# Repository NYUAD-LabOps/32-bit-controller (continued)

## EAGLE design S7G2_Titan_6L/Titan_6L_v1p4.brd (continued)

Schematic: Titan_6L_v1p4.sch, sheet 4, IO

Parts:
J8, J9, J11, J23, J25, J26, J27, J28, J29, J30, J31, J32, J33, J34: CONN_530470210_PICOBLADE_X_2; CON_530470210_MOL
J10, J13, J14, J15, J16, J17, J18, J19, J20, J21, J22, J24: CONN_530470410_PICOBLADE_X_4; CON_530470410_MOL
J12: 10-pos; 2X5
LED3, LED4, LED5, LED6, LED7, LED8, LED9, LED10, LED11, LED12, LED13, LED14, LED15, LED16: Green; 0805
R1, R2, R96, R97, R102, R103, R105, R106: 100K; 0402
R3, R12, R91, R93: 500R0; 0402
R4, R8, R61, R67, R70, R73, R78, R81, R84, R88: 2.2K; 0402
R6, R9, R11, R27, R62, R68, R71, R76, R79, R82, R85, R89, R92, R95: 470R0; 0402
R7, R10, R63, R69, R72, R77, R80, R83, R86, R90: 10K0; 0402
R28, R29, R30, R31, R32, R33, R34, R35, R36, R37, R38, R39, R40, R41, R42, R43, R44, R45, R46, R47, R48, R49, R50, R51, R52, R53, R54, R55, R56, R57, R58, R59, R60, R64, R65, R66: 33R0; 0402
TH01, TH02, TH03, TH04, TH05, TH06, TH07, TH08: CONN_530470210_PICOBLADE_X_2; CON_530470210_MOL
U7, U8, U9, U10, U11, U12, U13, U14, U15, U16, U17, U18, U19, U20, U21, U22, U23, U24, U25, U26, U27, U28, U29, U30, U31, U32, U33, U34, U35, U36, U37, U38, U39, U40, U41, U42, U43, U44, U45, U46, U47, U48, U49, U50, U51, U52, U53, U54, U55, U56: BC846BW; SOT323

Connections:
ESTOP: R89.2, R90.2, U53.2 (E(1)); also elsewhere on the board
GND: J8.1, J9.1, J10.1, J13.1, J14.1, J15.1, J16.1, J17.1, J18.1, J19.1, J20.1, J21.1, J22.1, J23.1, J24.1, J25.1, J26.1, J27.1, J28.1, J29.1, J30.1, J31.1, LED3.2 (C), LED4.2 (C), LED6.2 (C), LED7.2 (C), LED8.2 (C), LED9.2 (C), LED10.2 (C), LED11.2 (C), LED12.2 (C), LED13.2 (C), R7.1, R10.1, R63.1, R69.1, R72.1, R77.1, R80.1, R83.1, R86.1, R90.1, TH01.1, TH02.1, TH03.1, TH04.1, TH05.1, TH06.1, TH07.1, TH08.1, U9.2 (E(1)), U10.2 (E(1)), U11.2 (E(1)), U12.2 (E(1)), U13.2 (E(1)), U14.2 (E(1)), U15.2 (E(1)), U16.2 (E(1)), U17.2 (E(1)), U18.2 (E(1)), U19.2 (E(1)), U20.2 (E(1)), U21.2 (E(1)), U22.2 (E(1)), U23.2 (E(1)), U24.2 (E(1)), U25.2 (E(1)), U26.2 (E(1)), U27.2 (E(1)), U28.2 (E(1)), U29.2 (E(1)), U30.2 (E(1)), U31.2 (E(1)), U32.2 (E(1)), U33.2 (E(1)), U34.2 (E(1)), U35.2 (E(1)), U36.2 (E(1)), U37.2 (E(1)), U38.2 (E(1)), U39.2 (E(1)), U40.2 (E(1)), U41.2 (E(1)), U42.2 (E(1)), U45.2 (E(1)), U46.2 (E(1)), U47.2 (E(1)), U54.2 (E(1)), U55.2 (E(1)), U56.2 (E(1)); also elsewhere on the board
LS_01: R6.2, R7.2, U7.2 (E(1)); also elsewhere on the board
LS_02: R9.2, R10.2, U8.2 (E(1)); also elsewhere on the board
LS_03: R62.2, R63.2, U43.2 (E(1)); also elsewhere on the board
LS_04: R68.2, R69.2, U44.2 (E(1)); also elsewhere on the board
LS_05: R71.2, R72.2, U48.2 (E(1)); also elsewhere on the board
LS_06: R76.2, R77.2, U49.2 (E(1)); also elsewhere on the board
LS_07: R79.2, R80.2, U50.2 (E(1)); also elsewhere on the board
LS_08: R82.2, R83.2, U51.2 (E(1)); also elsewhere on the board
LS_09: R85.2, R86.2, U52.2 (E(1)); also elsewhere on the board
LS_RET: J8.2, J9.2, J23.2, J25.2, J26.2, J27.2, J28.2, J29.2, J30.2, J31.2, R4.1, R8.1, R61.1, R67.1, R70.1, R73.1, R78.1, R81.1, R84.1, R88.1
M1_DIR: R29.1; also elsewhere on the board
M1_ENABLE: R30.1; also elsewhere on the board
M1_STEP: R28.1; also elsewhere on the board
M2_DIR: R32.1; also elsewhere on the board
M2_ENABLE: R33.1; also elsewhere on the board
M2_STEP: R31.1; also elsewhere on the board
M3_DIR: R35.1; also elsewhere on the board
M3_ENABLE: R36.1; also elsewhere on the board
M3_STEP: R34.1; also elsewhere on the board
M4_DIR: R38.1; also elsewhere on the board
M4_ENABLE: R39.1; also elsewhere on the board
M4_STEP: R37.1; also elsewhere on the board
M5_DIR: R41.1; also elsewhere on the board
M5_ENABLE: R42.1; also elsewhere on the board
M5_STEP: R40.1; also elsewhere on the board
M6_DIR: R47.1; also elsewhere on the board
M6_ENABLE: R48.1; also elsewhere on the board
M6_STEP: R46.1; also elsewhere on the board
M7_DIR: R53.1; also elsewhere on the board
M7_ENABLE: R54.1; also elsewhere on the board
M7_STEP: R52.1; also elsewhere on the board
M8_DIR: R59.1; also elsewhere on the board
M8_ENABLE: R60.1; also elsewhere on the board
M8_STEP: R58.1; also elsewhere on the board
M9_DIR: R44.1; also elsewhere on the board
M9_ENABLE: R45.1; also elsewhere on the board
M9_STEP: R43.1; also elsewhere on the board
M10_DIR: R56.1; also elsewhere on the board
M10_ENABLE: R57.1; also elsewhere on the board
M10_STEP: R55.1; also elsewhere on the board
M11_DIR: R65.1; also elsewhere on the board
M11_ENABLE: R66.1; also elsewhere on the board
M11_STEP: R64.1; also elsewhere on the board
M12_DIR: R50.1; also elsewhere on the board
M12_ENABLE: R51.1; also elsewhere on the board
M12_STEP: R49.1; also elsewhere on the board
MO_DIR: J10.3, J13.3, J14.3, J15.3, J16.3, J17.3, J18.3, J19.3, J20.3, J21.3, J22.3, J24.3, U10.3 (C(3)), U13.3 (C(3)), U16.3 (C(3)), U19.3 (C(3)), U22.3 (C(3)), U25.3 (C(3)), U28.3 (C(3)), U31.3 (C(3)), U34.3 (C(3)), U37.3 (C(3)), U40.3 (C(3)), U46.3 (C(3))
MO_ENABLE: J10.2, J13.2, J14.2, J15.2, J16.2, J17.2, J18.2, J19.2, J20.2, J21.2, J22.2, J24.2, U11.3 (C(3)), U14.3 (C(3)), U17.3 (C(3)), U20.3 (C(3)), U23.3 (C(3)), U26.3 (C(3)), U29.3 (C(3)), U32.3 (C(3)), U35.3 (C(3)), U38.3 (C(3)), U41.3 (C(3)), U47.3 (C(3))
MO_STEP: J10.4, J13.4, J14.4, J15.4, J16.4, J17.4, J18.4, J19.4, J20.4, J21.4, J22.4, J24.4, U9.3 (C(3)), U12.3 (C(3)), U15.3 (C(3)), U18.3 (C(3)), U21.3 (C(3)), U24.3 (C(3)), U27.3 (C(3)), U30.3 (C(3)), U33.3 (C(3)), U36.3 (C(3)), U39.3 (C(3)), U45.3 (C(3))
unnamed: R4.2, U7.1 (B(2))
unnamed: LED3.1 (A), R6.1
unnamed: R29.2, U10.1 (B(2))
unnamed: R30.2, U11.1 (B(2))
unnamed: R28.2, U9.1 (B(2))
unnamed: R32.2, U13.1 (B(2))
unnamed: R33.2, U14.1 (B(2))
unnamed: R31.2, U12.1 (B(2))
unnamed: R35.2, U16.1 (B(2))
unnamed: R36.2, U17.1 (B(2))
unnamed: R34.2, U15.1 (B(2))
unnamed: R38.2, U19.1 (B(2))
unnamed: R39.2, U20.1 (B(2))
unnamed: R37.2, U18.1 (B(2))
unnamed: R41.2, U22.1 (B(2))
unnamed: R42.2, U23.1 (B(2))
unnamed: R40.2, U21.1 (B(2))
unnamed: R44.2, U25.1 (B(2))
unnamed: R45.2, U26.1 (B(2))
unnamed: R43.2, U24.1 (B(2))
unnamed: R47.2, U28.1 (B(2))
unnamed: R48.2, U29.1 (B(2))
unnamed: R46.2, U27.1 (B(2))
unnamed: R50.2, U31.1 (B(2))
unnamed: R51.2, U32.1 (B(2))
unnamed: R49.2, U30.1 (B(2))
unnamed: R53.2, U34.1 (B(2))
unnamed: R54.2, U35.1 (B(2))
unnamed: R52.2, U33.1 (B(2))
unnamed: R56.2, U37.1 (B(2))
unnamed: R57.2, U38.1 (B(2))
unnamed: R55.2, U36.1 (B(2))
unnamed: R59.2, U40.1 (B(2))
unnamed: R60.2, U41.1 (B(2))
unnamed: R58.2, U39.1 (B(2))
unnamed: R8.2, U8.1 (B(2))
unnamed: LED4.1 (A), R9.1
unnamed: R65.2, U46.1 (B(2))
unnamed: R66.2, U47.1 (B(2))
unnamed: R64.2, U45.1 (B(2))
unnamed: R3.2, U42.1 (B(2))
unnamed: R61.2, U43.1 (B(2))
unnamed: LED6.1 (A), R62.1
unnamed: R67.2, U44.1 (B(2))
unnamed: LED7.1 (A), R68.1
unnamed: R70.2, U48.1 (B(2))
unnamed: LED8.1 (A), R71.1
unnamed: R73.2, U49.1 (B(2))
unnamed: LED9.1 (A), R76.1
unnamed: R78.2, U50.1 (B(2))
unnamed: LED10.1 (A), R79.1
unnamed: R81.2, U51.1 (B(2))
unnamed: LED11.1 (A), R82.1
unnamed: R84.2, U52.1 (B(2))
unnamed: LED12.1 (A), R85.1
unnamed: R88.2, U53.1 (B(2))
unnamed: LED13.1 (A), R89.1
unnamed: J11.2, LED5.2 (C), U42.3 (C(3))
unnamed: LED5.1 (A), R11.1
unnamed: R12.2, U54.1 (B(2))
unnamed: J32.2, LED14.2 (C), U54.3 (C(3))
unnamed: LED14.1 (A), R27.1
unnamed: R91.2, U55.1 (B(2))
unnamed: J33.2, LED15.2 (C), U55.3 (C(3))
unnamed: LED15.1 (A), R92.1
unnamed: R93.2, U56.1 (B(2))
unnamed: J34.2, LED16.2 (C), U56.3 (C(3))
unnamed: LED16.1 (A), R95.1
P0_02_TH_01: R1.1, TH01.2; also elsewhere on the board
P0_04_TH_02: R2.1, TH02.2; also elsewhere on the board
P0_05_TH_03: R102.1, TH03.2; also elsewhere on the board
P0_06_TH_04: R103.1, TH04.2; also elsewhere on the board
P0_08_TH_05: R105.1, TH05.2; also elsewhere on the board
P0_09_TH_06: R106.1, TH06.2; also elsewhere on the board
P0_14_TH_07: R96.1, TH07.2; also elsewhere on the board
P0_15_TH_08: R97.1, TH08.2; also elsewhere on the board
P3_10: J12.1; also elsewhere on the board
P3_11: J12.2; also elsewhere on the board
P3_12: J12.3; also elsewhere on the board
P3_15: J12.10; also elsewhere on the board
P9_00: J12.9; also elsewhere on the board
P9_01: J12.8; also elsewhere on the board
P9_05: J12.4; also elsewhere on the board
P9_06: J12.5; also elsewhere on the board
P9_07: J12.6; also elsewhere on the board
P9_08: J12.7; also elsewhere on the board
RELAY_01: R93.1; also elsewhere on the board
RELAY_02: R91.1; also elsewhere on the board
RELAY_03: R12.1; also elsewhere on the board
RELAY_04: R3.1; also elsewhere on the board
VDD: R1.2, R2.2, R96.2, R97.2, R102.2, R103.2, R105.2, R106.2, U7.3 (C(3)), U8.3 (C(3)), U43.3 (C(3)), U44.3 (C(3)), U48.3 (C(3)), U49.3 (C(3)), U50.3 (C(3)), U51.3 (C(3)), U52.3 (C(3)), U53.3 (C(3)); also elsewhere on the board
VDD5: J11.1, J32.1, J33.1, J34.1, R11.2, R27.2, R92.2, R95.2; also elsewhere on the board

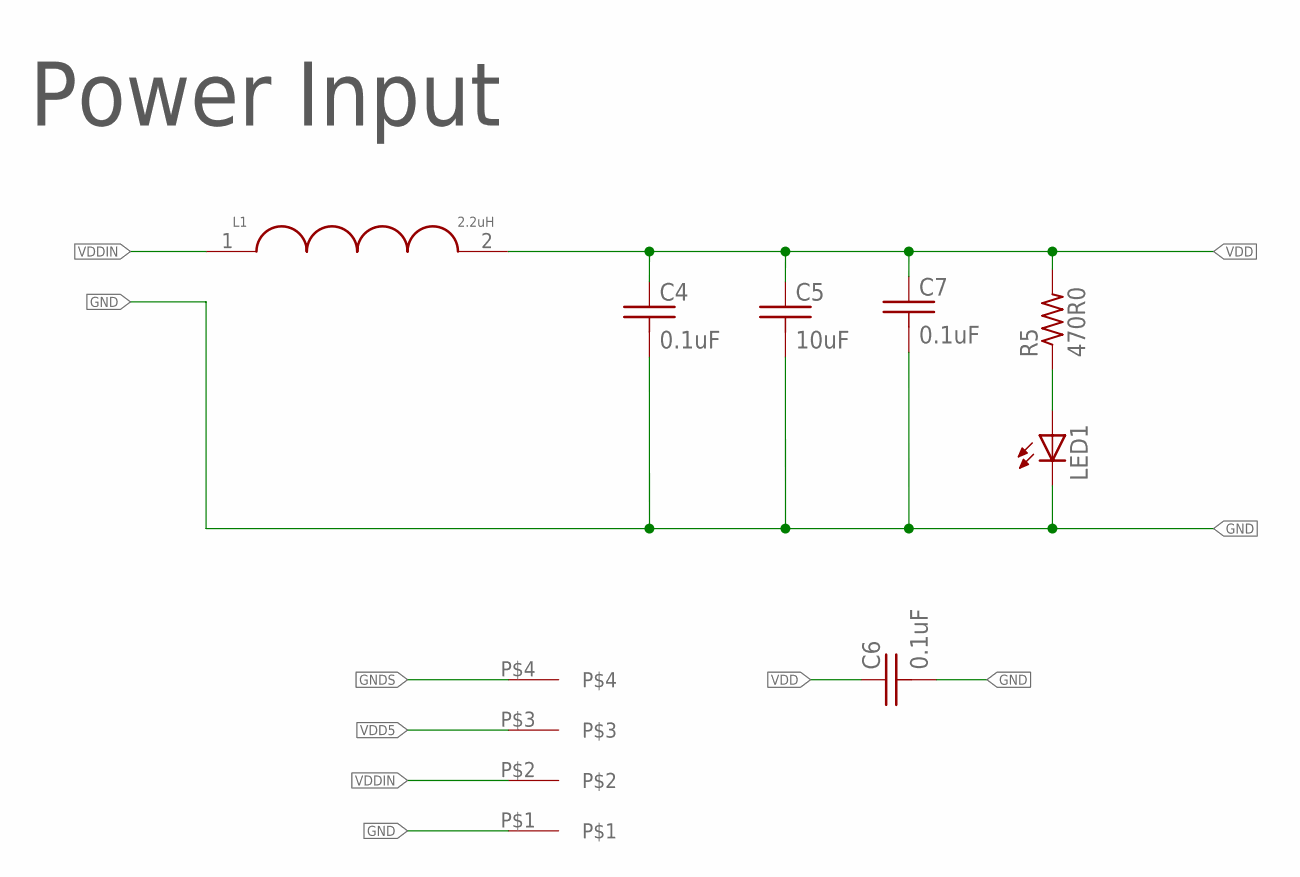
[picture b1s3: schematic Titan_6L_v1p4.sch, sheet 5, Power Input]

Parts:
C4, C6, C7: 0.1uF; 0402
C5: 10uF; 0402
J2: 4-pos; 1X4_3.81MM_PITCH
L1: 2.2uH; 1008
LED1: Green; 0805
R5: 470R0; 0402

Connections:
GND: C4.2, C5.2, C6.2, C7.2, J2.P$1, LED1.2 (C); also elsewhere on the board
GNDS: J2.P$4; also elsewhere on the board
unnamed: LED1.1 (A), R5.1
VDD: C4.1, C5.1, C6.1, C7.1, L1.2, R5.2; also elsewhere on the board
VDD5: J2.P$3; also elsewhere on the board
VDDIN: J2.P$2, L1.1

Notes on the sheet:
Power Input

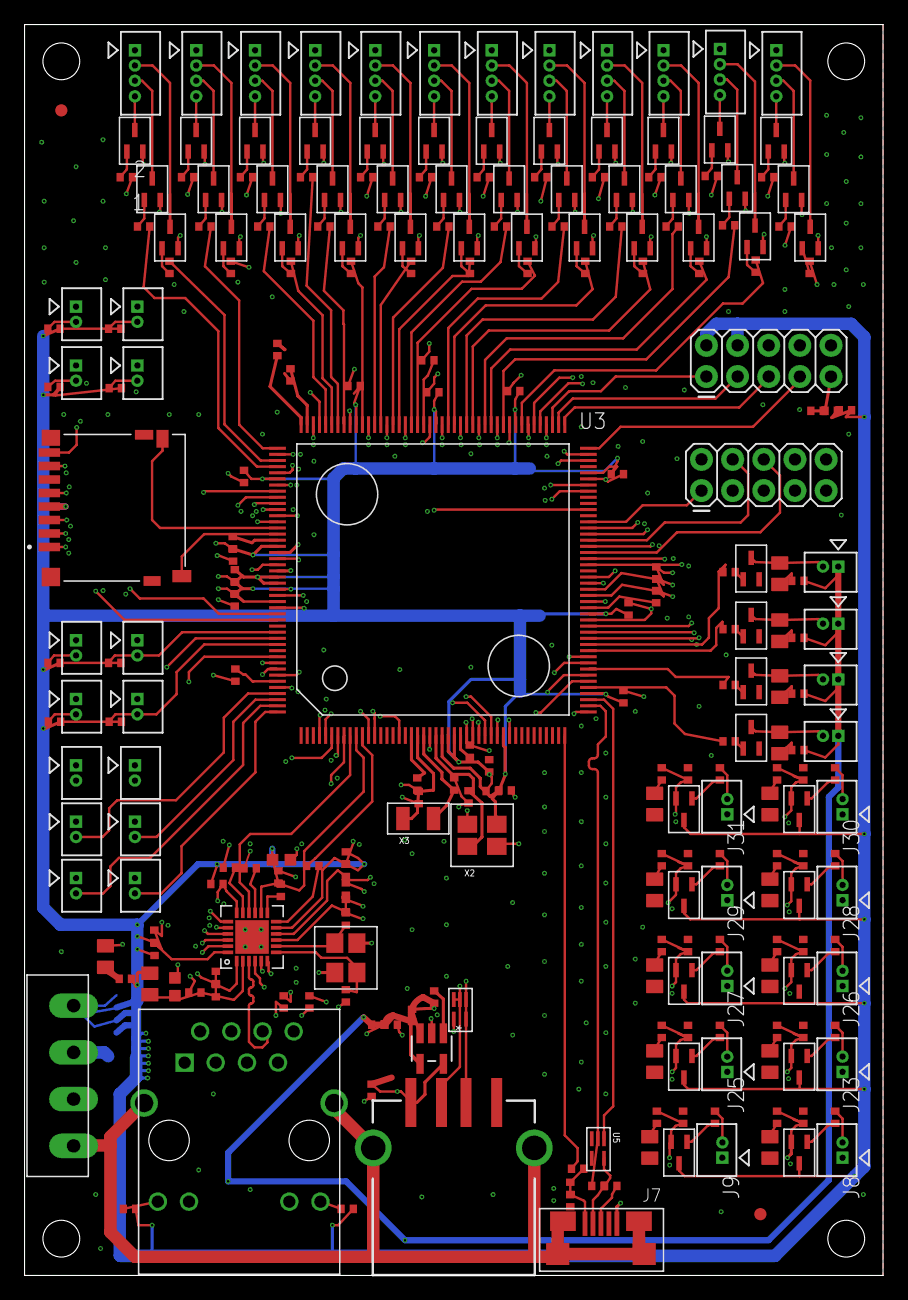
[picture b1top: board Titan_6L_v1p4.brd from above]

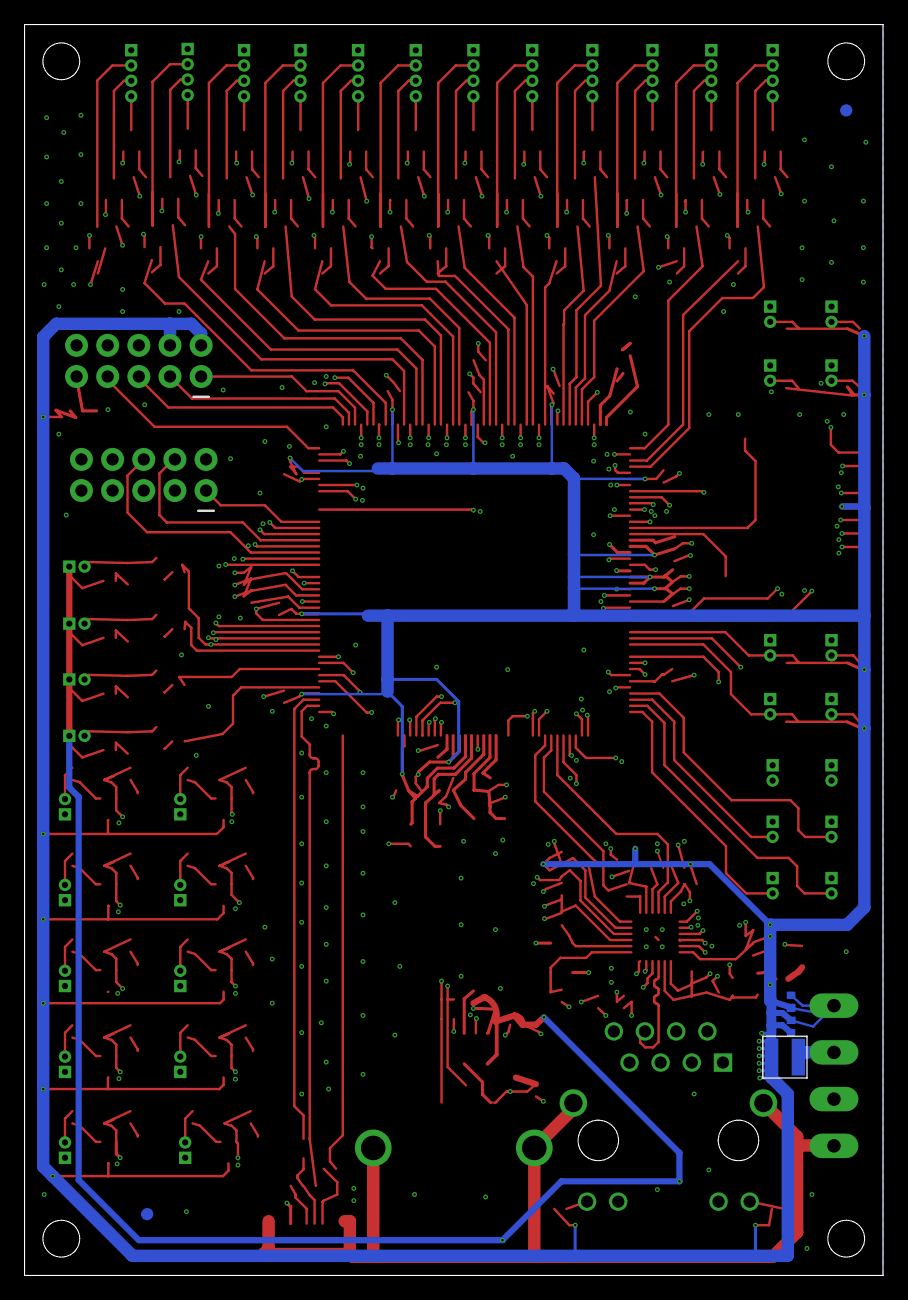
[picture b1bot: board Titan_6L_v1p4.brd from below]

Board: 6 copper layers, 70.0 x 102.0 mm, 275 parts (6 on the bottom side), 219 nets.

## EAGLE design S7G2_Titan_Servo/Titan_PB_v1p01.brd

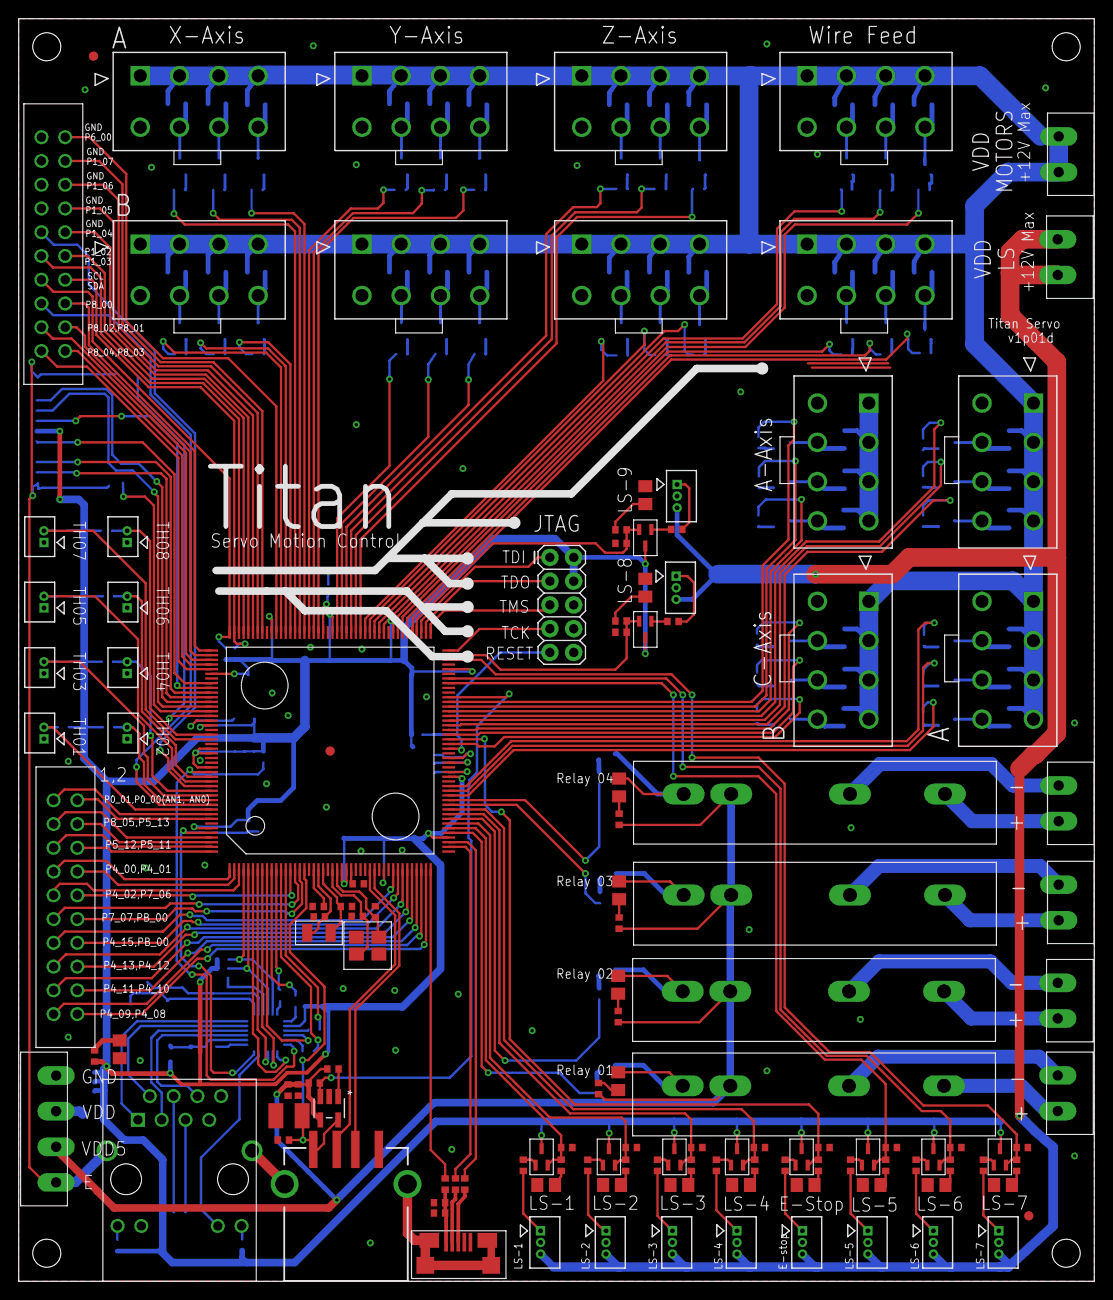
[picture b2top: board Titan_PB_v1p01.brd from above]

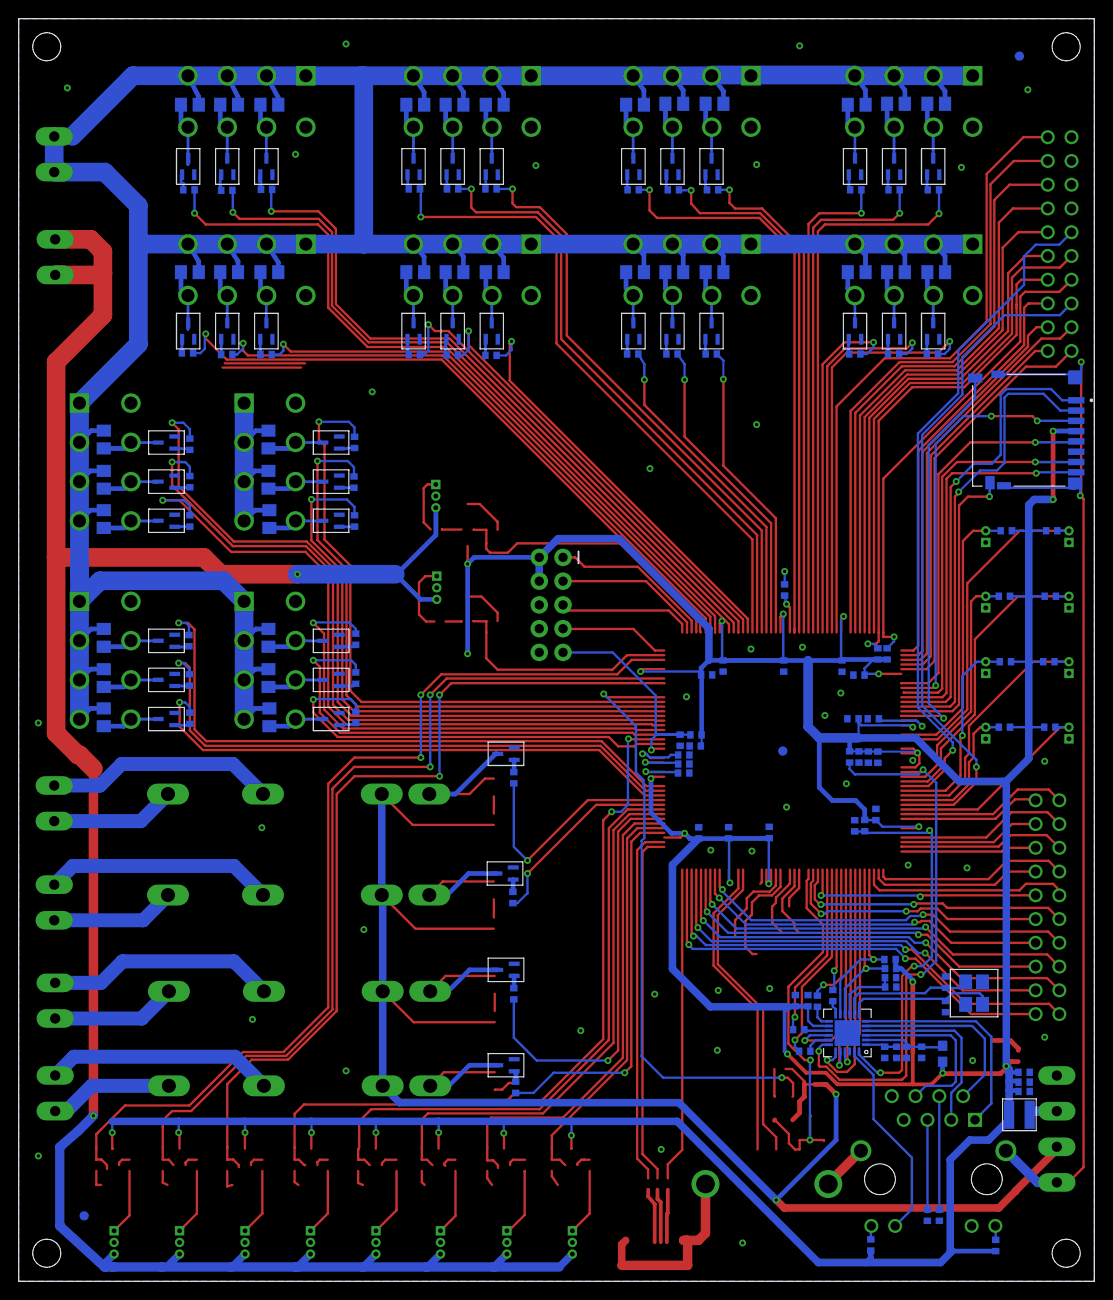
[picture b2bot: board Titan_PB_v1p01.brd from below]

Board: 2 copper layers, 115.0 x 135.0 mm, 312 parts (181 on the bottom side), 290 nets.

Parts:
AFID1, AFID2, AFID3, AFID4, AFID5, AFID6: FIDUCIAL_1MM
C1, C2: 24pF; 0402
C3: 100pF; 0402
C4, C7, C9, C10, C12, C13, C15, C19, C20, C22, C24, C25, C26, C27, C29, C30, C33, C34, C35, C36, C38, C39, C40, C42, C43: 0.1uF; 0402
C5, C6, C16, C23: 10uF; 0402
C8, C14: 22uF; 0402
C11: 2.2uF; 0402
C17, C18: 18pF; 0402
C21, C28, C41: 1uF; 0402
C31: 100uF_Tant; C1210
C32, C37: 12pF; 0402
FB1: FB2_603; 0603
J1: SD_CARD
J2: 4-pos; 1X4_3.81MM_PITCH
J3: 10-pos; 2X5
J4: 20-pos; 2_X_10_.1_INCH
J5, J10, J11, J12, J19, J20, J27, J28, J31, J32: CON_530470310_MOL
J6: USB-A; USB_A_SMT
J7: USB-B-Micro; USB_MICRO-B
J8: 2_X_10_.1_INCH
J9, J15, J16, J23, J24, J35: 2-pos; 2_3.81MM_PITCH
J13, J14, J17, J18, J21, J22, J25, J26, J29, J30, J33, J34: CON_39281083
L1: 2.2uH; 1008
LED1, LED3, LED4, LED5, LED6, LED7, LED8, LED9, LED10, LED11, LED12, LED13, LED14, LED15, LED16: Green; 0805
R1: 6K49; 0402
R2, R3, R13, R19, R20, R23, R24, R34, R53, R56, R59, R74, R77, R80, R83, R98, R101: 10K0; 0402
R4, R6: 1K5; 0402
R5, R7, R8, R29, R30, R31, R32, R33, R36, R49, R50, R51, R52, R55, R58, R73, R76, R79, R82, R97, R100: 470R0; 0402
R9, R10, R11, R12, R38, R39, R40, R44, R45, R46, R62, R63, R64, R68, R69, R70, R86, R87, R88, R92, R93, R94, R110, R111, R112, R116, R117, R118, R134, R135, R136, R140, R141, R142, R158, R159, R160, R164, R165, R166: 33R0; 0402
R14, R15: 1K0; 0402
R16: 15K0; 0402
R17, R18: 27R0; 0402
R21: 30K0; 0402
R22, R28, R35, R54, R57, R60, R75, R78, R81, R84, R99: 2K2; 0402
R25, R27, R102, R103, R105, R106, R107, R108: 100K; 0402
R37, R41, R42, R43, R47, R48, R61, R65, R66, R67, R71, R72, R85, R89, R90, R91, R95, R96, R109, R113, R114, R115, R119, R120, R133, R137, R138, R139, R143, R144, R157, R161, R162, R163, R167, R168: 1k; 0805
RJ1: RJ45; RJ45_TH_ELEC
TH01, TH02, TH03, TH04, TH05, TH06, TH07, TH08: CON_530470210_MOL
U1: KSZ8081_QFN_24; QFN-24-M
U2: AP2151DWG-7; SOT-23-5
U3: S7G2LQFP176; LQFP176_24X24
U5, U6, U7, U8, U9, U10, U11, U12, U13, U14, U15, U16, U17, U18, U19, U20, U21, U22, U23, U24, U25, U26, U27, U28, U29, U30, U34, U35, U36, U37, U38, U39, U46, U47, U48, U49, U50, U51, U58, U59, U60, U61, U62, U63, U70, U71, U72, U73, U74, U75: NPN; SOT323
U$1, U$2, U$7, U$8: RELAY_KYOTO_KF0604D
X1: 25MHz; SMD_3225
X2: 24MHz; SMD_3225
X3: 32.768KHz; SMD_X_2_PADS

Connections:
A_A_DIR: R111.P$1, U3.73
A_A_ENABLE: R112.P$1, U3.72
A_A_MI_DIR: J25.7, R113.1, U47.3
A_A_MI_ENABLE: J25.8, R114.1, U48.3
A_A_MI_STEP: J25.6, R109.1, U46.3
A_A_STEP: R110.P$1, U3.74
A_B_DIR: R117.P$1, U3.76
A_B_ENABLE: R118.P$1, U3.75
A_B_MI_DIR: J26.7, R119.1, U50.3
A_B_MI_ENABLE: J26.8, R120.1, U51.3
A_B_MI_STEP: J26.6, R115.1, U49.3
A_B_STEP: R116.P$1, U3.77
B_MI_DIR: J34.7, R167.1, U74.3
C58: C12.P$1, RJ1.4
C60: C13.P$1, RJ1.5
CRS_DV: R12.P$2, U1.15
C_A_DIR: R135.P$1, U3.58
C_A_ENABLE: R136.P$1, U3.57
C_A_MI_DIR: J29.7, R137.1, U59.3
C_A_MI_ENABLE: J29.8, R138.1, U60.3
C_A_MI_STEP: J29.6, R133.1, U58.3
C_A_STEP: R134.P$1, U3.59
C_B_DIR: R141.P$1, U3.70
C_B_ENABLE: R142.P$1, U3.68
C_B_MI_DIR: J30.7, R143.1, U62.3
C_B_MI_ENABLE: J30.8, R144.1, U63.3
C_B_MI_STEP: J30.6, R139.1, U61.3
C_B_STEP: R140.P$1, U3.71
D+: J7.P$3, R18.P$2
D-: J7.P$2, R17.P$2
ESTOP: R79.P$2, R80.P$2, U3.69, U21.2
ESTOP_RET: J20.1, R78.P$1
ETH: U1.16, U3.9
ETH_CRS_DV: R12.P$1, U3.13
ETH_IRQ14: R2.P$1, U1.18, U3.159
ETH_MDC: R4.P$1, U1.11, U3.4
ETH_MDIO: R6.P$1, U1.10, U3.5
ETH_RESET: C6.P$1, R3.P$1, U1.24, U3.172
ETH_RXD0: R10.P$1, U3.10
ETH_RXD1: R9.P$1, U3.11
ETH_RX_ER: R11.P$1, U3.12
ETH_TXD0: U1.20, U3.8
ETH_TXD1: U1.21, U3.7
ETH_TXD_EN: U1.19, U3.6
GND: C1.P$2, C2.P$2, C3.P$2, C4.P$2, C5.P$2, C6.P$2, C7.P$2, C8.P$2, C9.P$2, C10.P$2, C11.P$2, C12.P$2, C13.P$2, C14.P$2, C15.P$2, C16.P$2, C17.P$2, C18.P$2, C19.P$1, C20.P$1, C21.P$1, C22.P$1, C23.P$2, C24.P$1, C25.P$1, C26.P$2, C27.P$1, C28.P$2, C29.P$2, C30.P$1, C31.2, C32.P$2, C33.P$2, C34.P$1, C35.P$1, C36.P$2, C37.P$2, C38.P$1, C39.P$2, C40.P$2, C41.P$2, C42.P$2, C43.P$1, J1.6, J2.P$1, J3.6, J3.8, J3.10, J5.2, J6.GND, J7.P$5, J8.P$14, J8.P$16, J8.P$18, J8.P$20, J10.2, J11.2, J12.2, J19.2, J20.2, J27.2, J28.2, J31.2, J32.2, LED1.2, LED3.2, LED6.2, LED7.2, LED10.2, LED11.2, LED12.2, LED13.2, LED14.2, LED15.2, LED16.2, R1.P$1, R21.P$1, R22.P$1, R23.P$1, R24.P$1, R34.P$1, R53.P$1, R56.P$1, R59.P$1, R74.P$1, R77.P$1, R80.P$1, R83.P$1, R98.P$1, R101.P$1, RJ1.8, RJ1.10, TH01.1, TH02.1, TH03.1, TH04.1, TH05.1, TH06.1, TH07.1, TH08.1, U1.22, U1.25, U2.2, U3.22, U3.28, U3.29, U3.30, U3.33, U3.35, U3.45, U3.60, U3.63, U3.66, U3.83, U3.98, U3.111, U3.124, U3.139, U3.150, U3.153, U3.156, U3.157, U3.170, U6.2, U7.2, U10.2, U11.2, U12.2, U13.2, U14.2, U15.2, U16.2, U17.2, U22.2, U23.2, U24.2, U25.2, U26.2, U27.2, U34.2, U35.2, U36.2, U37.2, U38.2, U39.2, U46.2, U47.2, U48.2, U49.2, U50.2, U51.2, U58.2, U59.2, U60.2, U61.2, U62.2, U63.2, U70.2, U71.2, U72.2, U73.2, U74.2, U75.2, X1.2, X1.4, X2.2, X2.4
GNDE: J1.S1, J1.S2, J1.S3, J1.S4, J2.P$4, J6.SHLD1, J6.SHLD2, J7.P$6, J7.P$7, J7.P$8, J7.P$9, RJ1.13, RJ1.14
IIC_1_SCL: J8.P$8, R14.P$2, U3.132
IIC_1_SDA: J8.P$7, R15.P$2, U3.131
LED1/SPEED: RJ1.11, U1.23
LS_01: R33.P$2, R34.P$2, U3.50, U5.2
LS_01_RET: J32.1, R28.P$1
LS_02: R36.P$2, R53.P$2, U3.51, U8.2
LS_02_RET: J31.1, R35.P$1
LS_03: R55.P$2, R56.P$2, U3.53, U9.2
LS_03_RET: J28.1, R54.P$1
LS_04: R73.P$2, R74.P$2, U3.54, U19.2
LS_04_RET: J27.1, R60.P$1
LS_05: R58.P$2, R59.P$2, U3.81, U18.2
LS_05_RET: J19.1, R57.P$1
LS_06: R76.P$2, R77.P$2, U3.82, U20.2
LS_06_RET: J12.1, R75.P$1
LS_07: R97.P$2, R98.P$2, U3.86, U29.2
LS_07_RET: J11.1, R84.P$1
LS_08: R82.P$2, R83.P$2, U3.87, U28.2
LS_08_RET: J5.1, R81.P$1
LS_09: R100.P$2, R101.P$2, U3.92, U30.2
LS_09_RET: J10.1, R99.P$1
unnamed: C24.P$2, U3.148
unnamed: LED1.1, R5.P$1
unnamed: C33.P$1, U3.19
unnamed: C42.P$1, U3.62
unnamed: R23.P$2, U3.64
unnamed: R24.P$2, U3.65
unnamed: R22.P$2, U3.27
unnamed: R28.P$2, U5.1
unnamed: LED3.1, R33.P$1
unnamed: R35.P$2, U8.1
unnamed: LED6.1, R36.P$1
unnamed: R39.P$2, U11.1
unnamed: R40.P$2, U12.1
unnamed: R38.P$2, U10.1
unnamed: R45.P$2, U14.1
unnamed: R46.P$2, U15.1
unnamed: R44.P$2, U13.1
unnamed: R29.P$2, U6.1
unnamed: LED4.2, U6.3, U$1.P$1
unnamed: R30.P$2, U7.1
unnamed: LED5.2, U7.3, U$2.P$1
unnamed: LED5.1, R31.P$1
unnamed: LED4.1, R32.P$1
unnamed: R63.P$2, U23.1
unnamed: R64.P$2, U24.1
unnamed: R62.P$2, U22.1
unnamed: R69.P$2, U26.1
unnamed: R70.P$2, U27.1
unnamed: R68.P$2, U25.1
unnamed: R54.P$2, U9.1
unnamed: LED7.1, R55.P$1
unnamed: R57.P$2, U18.1
unnamed: LED10.1, R58.P$1
unnamed: R60.P$2, U19.1
unnamed: LED11.1, R73.P$1
unnamed: R87.P$2, U35.1
unnamed: R88.P$2, U36.1
unnamed: R86.P$2, U34.1
unnamed: R93.P$2, U38.1
unnamed: R94.P$2, U39.1
unnamed: R92.P$2, U37.1
unnamed: R49.P$2, U16.1
unnamed: LED8.2, U16.3, U$7.P$1
unnamed: R50.P$2, U17.1
unnamed: LED9.2, U17.3, U$8.P$1
unnamed: LED9.1, R51.P$1
unnamed: LED8.1, R52.P$1
unnamed: R111.P$2, U47.1
unnamed: R112.P$2, U48.1
unnamed: R110.P$2, U46.1
unnamed: R117.P$2, U50.1
unnamed: R118.P$2, U51.1
unnamed: R116.P$2, U49.1
unnamed: R75.P$2, U20.1
unnamed: LED12.1, R76.P$1
unnamed: R78.P$2, U21.1
unnamed: LED13.1, R79.P$1
unnamed: R81.P$2, U28.1
unnamed: LED14.1, R82.P$1
unnamed: R135.P$2, U59.1
unnamed: R136.P$2, U60.1
unnamed: R134.P$2, U58.1
unnamed: R141.P$2, U62.1
unnamed: R142.P$2, U63.1
unnamed: R140.P$2, U61.1
unnamed: R84.P$2, U29.1
unnamed: LED15.1, R97.P$1
unnamed: R99.P$2, U30.1
unnamed: LED16.1, R100.P$1
unnamed: R159.P$2, U71.1
unnamed: R160.P$2, U72.1
unnamed: R158.P$2, U70.1
unnamed: R165.P$2, U74.1
unnamed: R166.P$2, U75.1
unnamed: R164.P$2, U73.1
NC: RJ1.7, U3.79, U3.80, U3.85
P0_00: J4.P$2, U3.169
P0_01: J4.P$1, U3.168
P0_02_TH_01: R25.P$1, TH01.2, U3.167
P0_03: J8.P$6, U3.166
P0_04_TH_02: R27.P$1, TH02.2, U3.165
P0_05_TH_03: R102.P$1, TH03.2, U3.164
P0_06_TH_04: R103.P$1, TH04.2, U3.163
P0_07: J8.P$12, U3.162
P0_08_TH_05: R105.P$1, TH05.2, U3.161
P0_09_TH_06: R106.P$1, TH06.2, U3.160
P0_14_TH_07: R107.P$1, TH07.2, U3.152
P0_15_TH_08: R108.P$1, TH08.2, U3.151
P1_02: J8.P$10, U3.130
P1_03: J8.P$9, U3.129
P1_04: J8.P$11, U3.128
P1_05: J8.P$13, U3.127
P1_06: J8.P$15, U3.126
P1_07: J8.P$17, U3.125
P4_00: J4.P$7, U3.1
P4_01: J4.P$8, U3.2
P4_02: J4.P$9, U3.3
P4_08: J4.P$20, U3.43
P4_09: J4.P$19, U3.42
P4_10: J4.P$18, U3.41
P4_11: J4.P$17, U3.40
P4_12: J4.P$16, U3.39
P4_13: J4.P$15, U3.38
P4_14: J4.P$14, U3.37
P4_15: J4.P$13, U3.36
P5_11: J4.P$6, U3.176
P5_12: J4.P$5, U3.175
P5_13: J4.P$4, U3.174
P6_00: J8.P$19, U3.122
P7_06: J4.P$10, U3.14
P7_07: J4.P$11, U3.15
P8_00: J8.P$5, U3.133
P8_01: J8.P$3, U3.134
P8_02: J8.P$4, U3.135
P8_03: J8.P$1, U3.136
P8_04: J8.P$2, U3.137
P8_05: J4.P$3, U3.173
PB_00: J4.P$12, U3.16
R51: R7.P$1, RJ1.12
R52: R8.P$1, RJ1.9
RELAY_1: R29.P$1, U3.56
RELAY_2: R30.P$1, U3.55
RELAY_3: R49.P$1, U3.52
RELAY_4: R50.P$1, U3.49
RESET: C16.P$1, J3.9, R13.P$1, U3.67
REXT: C3.P$1, R1.P$2, U1.9
RO_NEG_1: J15.P$2, U$1.P$3
RO_NEG_2: J16.P$2, U$2.P$3
RO_NEG_3: J23.P$2, U$7.P$3
RO_NEG_4: J24.P$2, U$8.P$3
RO_POS_1: J15.P$1, U$1.P$4
RO_POS_2: J16.P$1, U$2.P$4
RO_POS_3: J23.P$1, U$7.P$4
RO_POS_4: J24.P$1, U$8.P$4
RXD0: R10.P$2, U1.13
RXD1: R9.P$2, U1.12
RXER: R11.P$2, U1.17
RXM: RJ1.6, U1.3
RXP: RJ1.3, U1.4
SD1_CD: J1.10, U3.146
SD1_CLK: J1.5, U3.140
SD1_CMD: J1.3, U3.141
SD1_DAT0: J1.7, U3.142
SD1_DAT1: J1.8, U3.143
SD1_DAT2: J1.1, U3.144
SD1_DAT3: J1.2, U3.145
SD1_WP: J1.9, U3.147
TCK: J3.7, U3.88
TDI: J3.1, U3.91
TDO: J3.3, U3.90
TMS: J3.5, U3.89
TXM: RJ1.2, U1.5
TXP: RJ1.1, U1.6
USBHS_FAULT: R19.P$1, U2.3, U3.78
USBHS_N: J6.D-, U3.31
USBHS_P: J6.D+, U3.32
USBHS_VBUS: C29.P$1, C31.1, J6.VBUS, U2.5, U3.17
USBHS_VBUSEN: R20.P$1, U2.1
USB_N: R17.P$1, U3.46
USB_P: R18.P$1, U3.47
USB_VBUS_B: R16.P$1, U3.44
VBUS: C28.P$1, J7.P$1, R16.P$2, R21.P$2
VCL_F(FLASH): C34.P$2, U3.112
VDD: C4.P$1, C5.P$1, C7.P$1, C14.P$1, C15.P$1, C19.P$2, C20.P$2, C21.P$2, C22.P$2, C25.P$2, C27.P$2, C30.P$2, C35.P$2, C36.P$1, C38.P$2, C39.P$1, C40.P$1, C41.P$1, C43.P$2, FB1.1, J1.4, J3.2, J3.4, L1.2, R2.P$2, R3.P$2, R4.P$2, R5.P$2, R6.P$2, R7.P$2, R8.P$2, R13.P$2, R14.P$1, R15.P$1, R25.P$2, R27.P$2, R102.P$2, R103.P$2, R105.P$2, R106.P$2, R107.P$2, R108.P$2, U1.14, U3.25, U3.26, U3.34, U3.48, U3.61, U3.84, U3.97, U3.110, U3.123, U3.138, U3.149, U3.154, U3.155, U3.158, U3.171, U5.3, U8.3, U9.3, U18.3, U19.3, U20.3, U21.3, U28.3, U29.3, U30.3
VDD5: C23.P$1, C26.P$1, J2.P$3, R19.P$2, R20.P$2, R31.P$2, R32.P$2, R51.P$2, R52.P$2, U2.4, U$1.P$2, U$2.P$2, U$7.P$2, U$8.P$2
VDDIN: J2.P$2, L1.1
VDDLS: J5.3, J10.3, J11.3, J12.3, J19.3, J20.3, J27.3, J28.3, J31.3, J32.3, J35.P$1, J35.P$2
VDDMTR: J9.P$1, J9.P$2, J13.1, J13.2, J13.3, J13.4, J14.1, J14.2, J14.3, J14.4, J17.1, J17.2, J17.3, J17.4, J18.1, J18.2, J18.3, J18.4, J21.1, J21.2, J21.3, J21.4, J22.1, J22.2, J22.3, J22.4, J25.1, J25.2, J25.3, J25.4, J26.1, J26.2, J26.3, J26.4, J29.1, J29.2, J29.3, J29.4, J30.1, J30.2, J30.3, J30.4, J33.1, J33.2, J33.3, J33.4, J34.1, J34.2, J34.3, J34.4, R37.2, R41.2, R42.2, R43.2, R47.2, R48.2, R61.2, R65.2, R66.2, R67.2, R71.2, R72.2, R85.2, R89.2, R90.2, R91.2, R95.2, R96.2, R109.2, R113.2, R114.2, R115.2, R119.2, R120.2, R133.2, R137.2, R138.2, R139.2, R143.2, R144.2, R157.2, R161.2, R162.2, R163.2, R167.2, R168.2
VDD_1.2: C10.P$1, C11.P$1, U1.1
VDD_ENET1: C8.P$1, C9.P$1, FB1.2, U1.2
WF_A_DIR: R159.P$1, U3.99
WF_A_ENABLE: R160.P$1, U3.96
WF_A_MI_DIR: J33.7, R161.1, U71.3
WF_A_MI_ENABLE: J33.8, R162.1, U72.3
WF_A_MI_STEP: J33.6, R157.1, U70.3
WF_A_STEP: R158.P$1, U3.100
WF_B_DIR: R165.P$1, U3.94
WF_B_ENABLE: R166.P$1, U3.93
WF_B_MI_ENABLE: J34.8, R168.1, U75.3
WF_B_MI_STEP: J34.6, R163.1, U73.3
WF_B_STEP: R164.P$1, U3.95
XCIN: C32.P$1, U3.20, X3.P$1
XCOUT: C37.P$1, U3.21, X3.P$2
XII: C1.P$1, U1.8, X1.1
XOO: C2.P$1, U1.7, X1.3
XTAL1: C17.P$1, U3.23, X2.1
XTAL2: C18.P$1, U3.24, X2.3
X_A_DIR: R39.P$1, U3.117
X_A_ENABLE: R40.P$1, U3.116
X_A_MI_DIR: J13.7, R41.1, U11.3
X_A_MI_ENABLE: J13.8, R42.1, U12.3
X_A_MI_STEP: J13.6, R37.1, U10.3
X_A_STEP: R38.P$1, U3.118
X_B_DIR: R45.P$1, U3.120
X_B_ENABLE: R46.P$1, U3.119
X_B_MI_DIR: J14.7, R47.1, U14.3
X_B_MI_ENABLE: J14.8, R48.1, U15.3
X_B_MI_STEP: J14.6, R43.1, U13.3
X_B_STEP: R44.P$1, U3.121
Y_A_DIR: R63.P$1, U3.114
Y_A_ENABLE: R64.P$1, U3.113
Y_A_MI_DIR: J17.7, R65.1, U23.3
Y_A_MI_ENABLE: J17.8, R66.1, U24.3
Y_A_MI_STEP: J17.6, R61.1, U22.3
Y_A_STEP: R62.P$1, U3.115
Y_B_DIR: R69.P$1, U3.108
Y_B_ENABLE: R70.P$1, U3.107
Y_B_MI_DIR: J18.7, R71.1, U26.3
Y_B_MI_ENABLE: J18.8, R72.1, U27.3
Y_B_MI_STEP: J18.6, R67.1, U25.3
Y_B_STEP: R68.P$1, U3.109
Z_A_DIR: R87.P$1, U3.105
Z_A_ENABLE: R88.P$1, U3.104
Z_A_MI_DIR: J21.7, R89.1, U35.3
Z_A_MI_ENABLE: J21.8, R90.1, U36.3
Z_A_MI_STEP: J21.6, R85.1, U34.3
Z_A_STEP: R86.P$1, U3.106
Z_B_DIR: R93.P$1, U3.102
Z_B_ENABLE: R94.P$1, U3.101
Z_B_MI_DIR: J22.7, R95.1, U38.3
Z_B_MI_ENABLE: J22.8, R96.1, U39.3
Z_B_MI_STEP: J22.6, R91.1, U37.3
Z_B_STEP: R92.P$1, U3.103
